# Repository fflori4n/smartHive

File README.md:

# smartHive
smart Hive sistem - ESP32 GSM base, that collects data from multiple atmell based field sensors and sends it via mqtt

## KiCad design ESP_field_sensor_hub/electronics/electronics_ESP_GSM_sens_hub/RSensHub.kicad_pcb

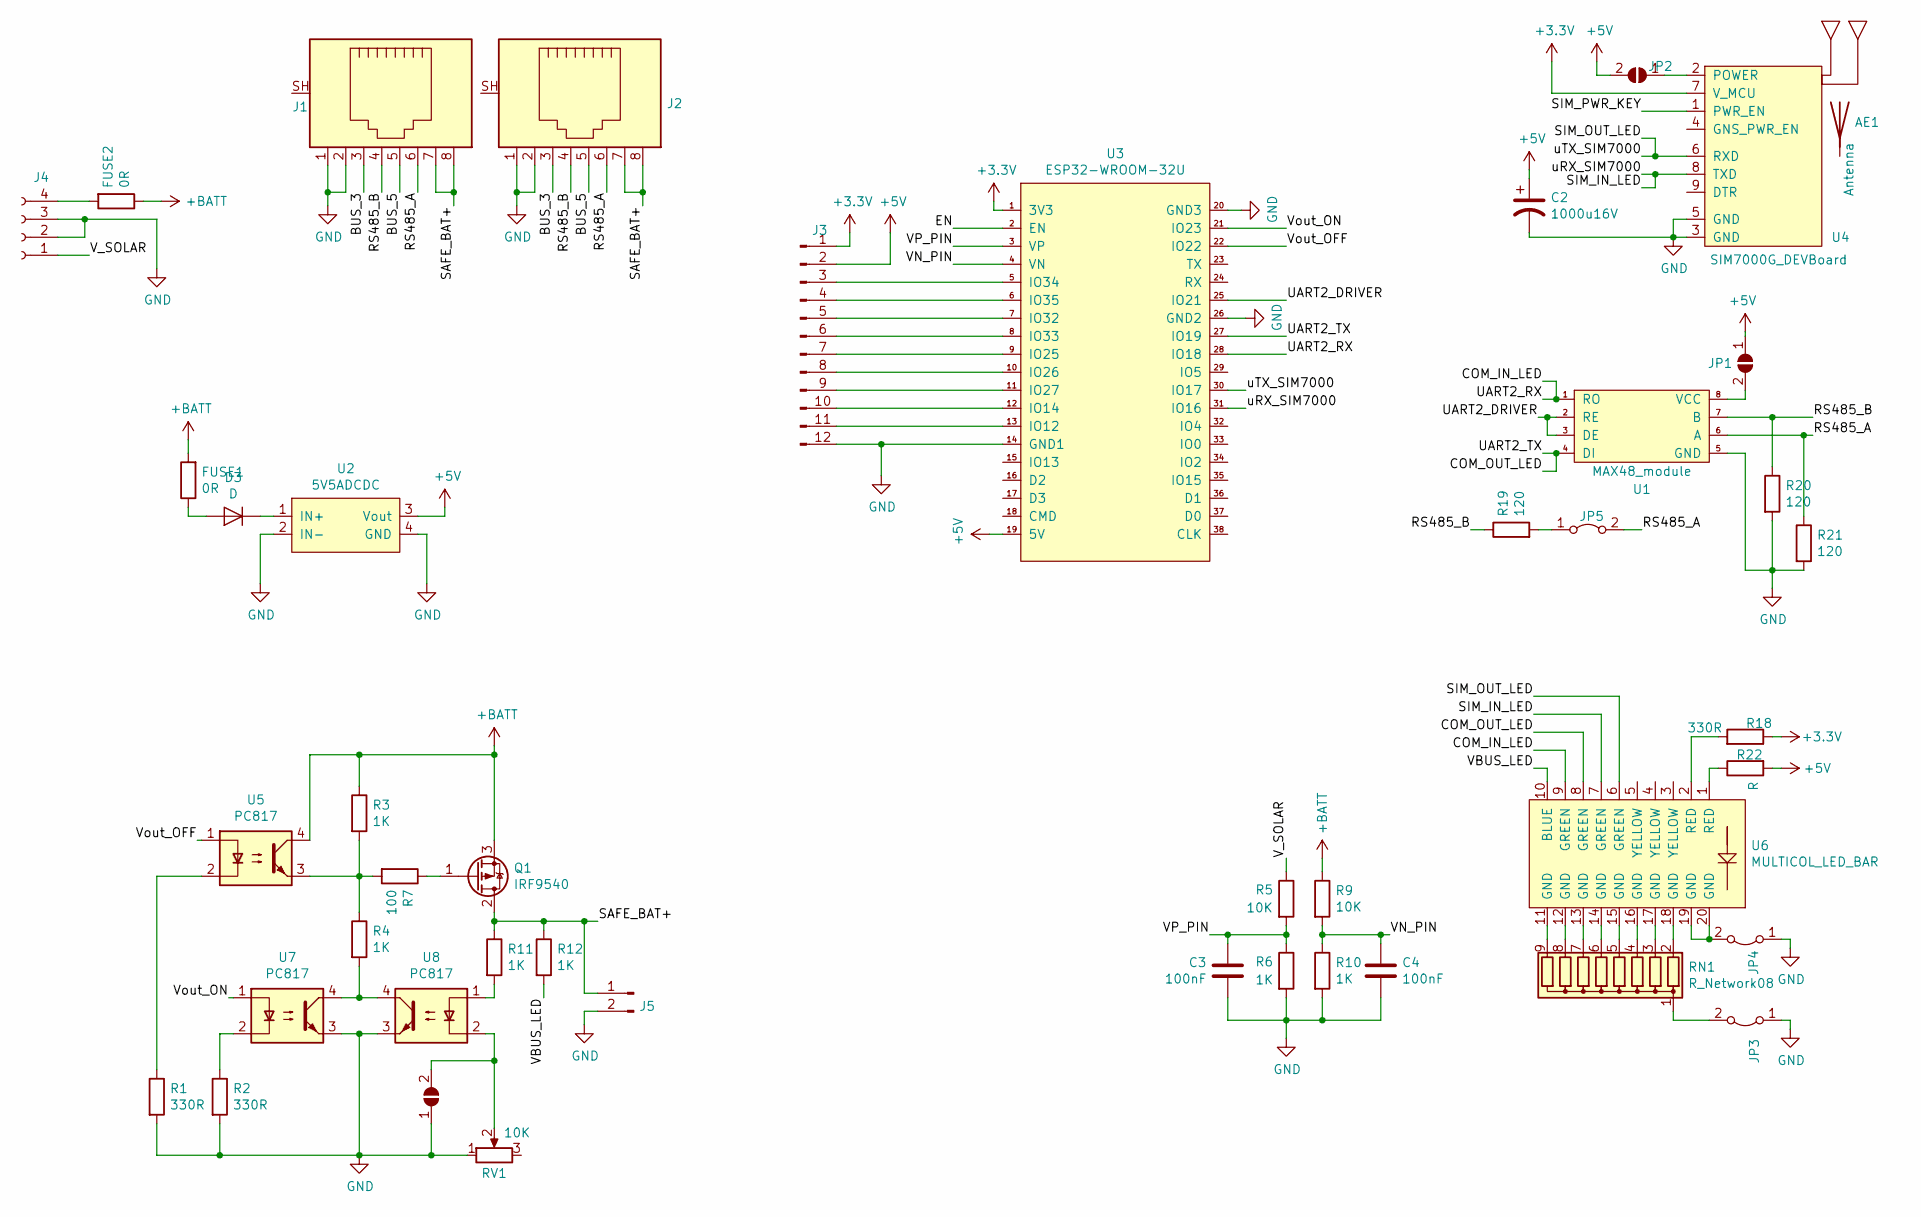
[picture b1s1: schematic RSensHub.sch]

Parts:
AE1: Antenna; GNSSantennaVertical
C2: 1000u16V; CAP_Radial_D10.0mm_P5.00mm
C3, C4: 100nF; Capker_L4.6mm_W2.0mm_P2.50mm
D3: D; 1N41_Diode
FUSE1, FUSE2: 0R; resistor0.25,9mm
J1, J2: RJ45_Shielded; RJ45
J3: Conn_01x12_Male; PinHeader_1x12_P2.54mm_widePads
J4: Conn_01x04_Female; TerminalBlockRemovablex4
J5: Conn_01x02_Male; TerminalBlockRemovablex2
JP1, JP2, JP6: SolderJumper_2_Open; SolderJumper-2_P1.3mm_Open_RoundedPad1.0x1.5mm
JP3, JP4: Jumper_2_Bridged; jumperx2_P2.54mm_widePads
JP5: RS485 terminator; jumperx2_P2.54mm_widePads
Q1: IRF9540; TO-220-3_Horizontal_TabDown_bothSides
R1, R2, R18: 330R; resistor0.25,9mm
R3, R4, R6, R10, R11, R12: 1K; resistor0.25,9mm
R5, R9: 10K; resistor0.25,9mm
R7: 100; resistor0.25,9mm
R19, R20, R21: 120; resistor0.25,9mm
R22: R; resistor0.25,9mm
RN1: R_Network08; PinHeader_1x9_P2.54mm_widePads
RV1: 10K; Potentiometer_ACP_CA9-V10_Vertical_Hole
U1: MAX48_module; MAX485_module
U2: 5V5ADCDC; DCDC_HCW_P715
U3: ESP32-WROOM-32U
U4: SIM7000G_DEVBoard; sim7000G_dev_board
U5, U7, U8: PC817; optoCouplerDIP4
U6: MULTICOL_LED_BAR; DIP-20_LED_BAR_DISP

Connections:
+3V3: J3.1, R18.1, U3.1 (3V3), U4.7 (V_MCU)
+5V: C2.1, J3.2, JP1.1 (A), JP2.2 (B), R22.2, U2.3 (Vout), U3.19 (5V)
+BATT: FUSE1.2, FUSE2.1, Q1.3 (S), R3.1, R9.1, U5.4; also elsewhere on the board
/BUS_3: J1.3, J2.3
/BUS_5: J1.5, J2.5
/COM_IN_LED: U1.1 (RO), U3.28 (IO18), U6.9 (GREEN)
/COM_OUT_LED: U1.4 (DI), U3.27 (IO19), U6.8 (GREEN)
/EN: U3.2 (EN)
/RS485_A: J1.6, J2.6, JP5.2 (B), R21.1, U1.6 (A)
/RS485_B: J1.4, J2.4, R19.1, R20.1, U1.7 (B)
/SAFE_BAT+: J1.7, J1.8, J2.7, J2.8, J5.1, Q1.2 (D), R11.1, R12.1
/SIM_IN_LED: U3.31 (IO16), U4.8 (TXD), U6.7 (GREEN)
/SIM_OUT_LED: U3.30 (IO17), U4.6 (RXD), U6.6 (GREEN)
/SIM_PWR_KEY: U4.1 (PWR_EN)
/UART2_DRIVER: U1.2 (RE), U1.3 (DE), U3.25 (IO21)
/VBUS_LED: R12.2, U6.10 (BLUE)
/VN_PIN: C4.1, R9.2, R10.1, U3.4 (VN)
/VP_PIN: C3.1, R5.2, R6.1, U3.3 (VP)
/V_SOLAR: J4.1, R5.1
/Vout_OFF: U3.22 (IO22), U5.1
/Vout_ON: U3.21 (IO23), U7.1
GND: C2.2, C3.2, C4.2, J1.1, J1.2, J2.1, J2.2, J3.12, J4.2, J4.3, J5.2, JP3.1 (A), JP4.1 (A), JP6.1 (A), R1.2, R2.2, R6.2, R10.2, R20.2, R21.2, RV1.1, U1.5 (GND), U2.2 (IN-), U2.4 (GND), U3.14 (GND1), U3.20 (GND3), U3.26 (GND2), U4.3 (GND), U4.5 (GND), U7.3, U8.3
unnamed: D3.1 (K), U2.1 (IN+)
unnamed 24: D3.2 (A), FUSE1.1; also elsewhere on the board
unnamed 25: FUSE2.2, J4.4; also elsewhere on the board
unnamed: J3.3, U3.5 (IO34)
unnamed: J3.4, U3.6 (IO35)
unnamed: J3.5, U3.7 (IO32)
unnamed: J3.6, U3.8 (IO33)
unnamed: J3.7, U3.9 (IO25)
unnamed: J3.8, U3.10 (IO26)
unnamed: J3.9, U3.11 (IO27)
unnamed: J3.10, U3.12 (IO14)
unnamed: J3.11, U3.13 (IO12)
unnamed: JP1.2 (B), U1.8 (VCC)
unnamed: JP2.1 (A), U4.2 (POWER)
unnamed: JP3.2 (B), RN1.1 (common)
unnamed: JP4.2 (B), U6.19 (GND), U6.20 (GND)
unnamed: JP5.1 (A), R19.2
unnamed: JP6.2 (B), RV1.2, U8.2
unnamed: Q1.1 (G), R7.1
unnamed: R1.1, U5.2
unnamed: R2.1, U7.2
unnamed: R3.2, R4.1, R7.2, U5.3
unnamed: R4.2, U7.4, U8.4
unnamed: R11.2, U8.1
unnamed: R18.2, U6.2 (RED)
unnamed: R22.1, U6.1 (RED)
unnamed: RN1.2 (R1), U6.18 (GND)
unnamed: RN1.3 (R2), U6.17 (GND)
unnamed: RN1.4 (R3), U6.16 (GND)
unnamed: RN1.5 (R4), U6.15 (GND)
unnamed: RN1.6 (R5), U6.14 (GND)
unnamed: RN1.7 (R6), U6.13 (GND)
unnamed: RN1.8 (R7), U6.12 (GND)
unnamed: RN1.9 (R8), U6.11 (GND)

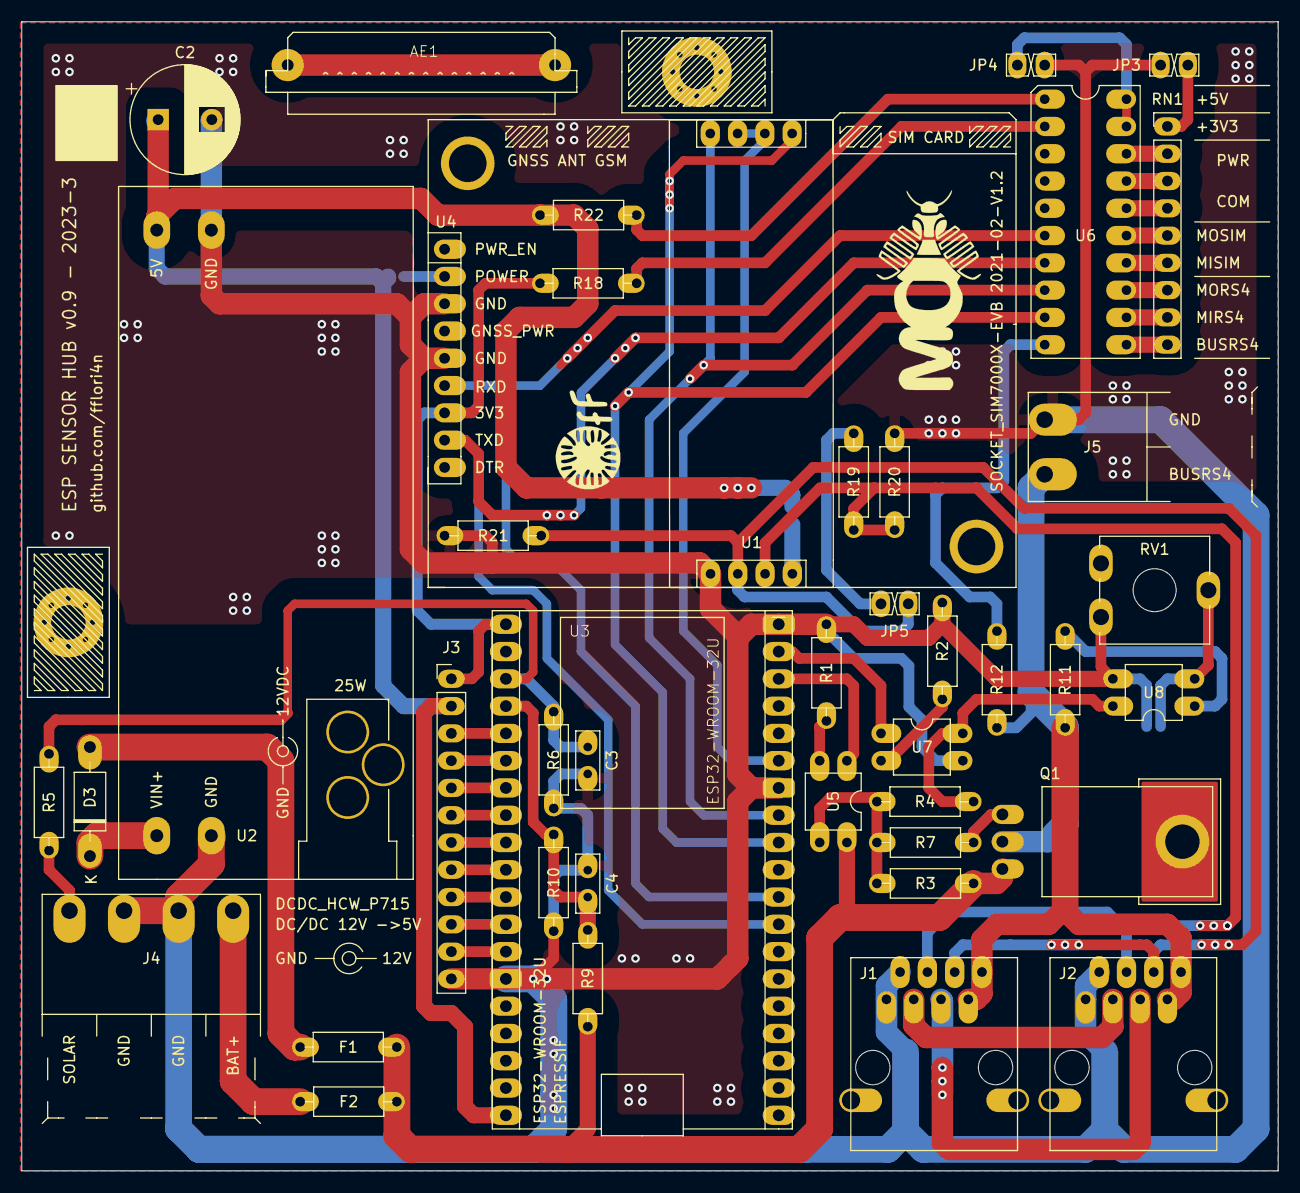
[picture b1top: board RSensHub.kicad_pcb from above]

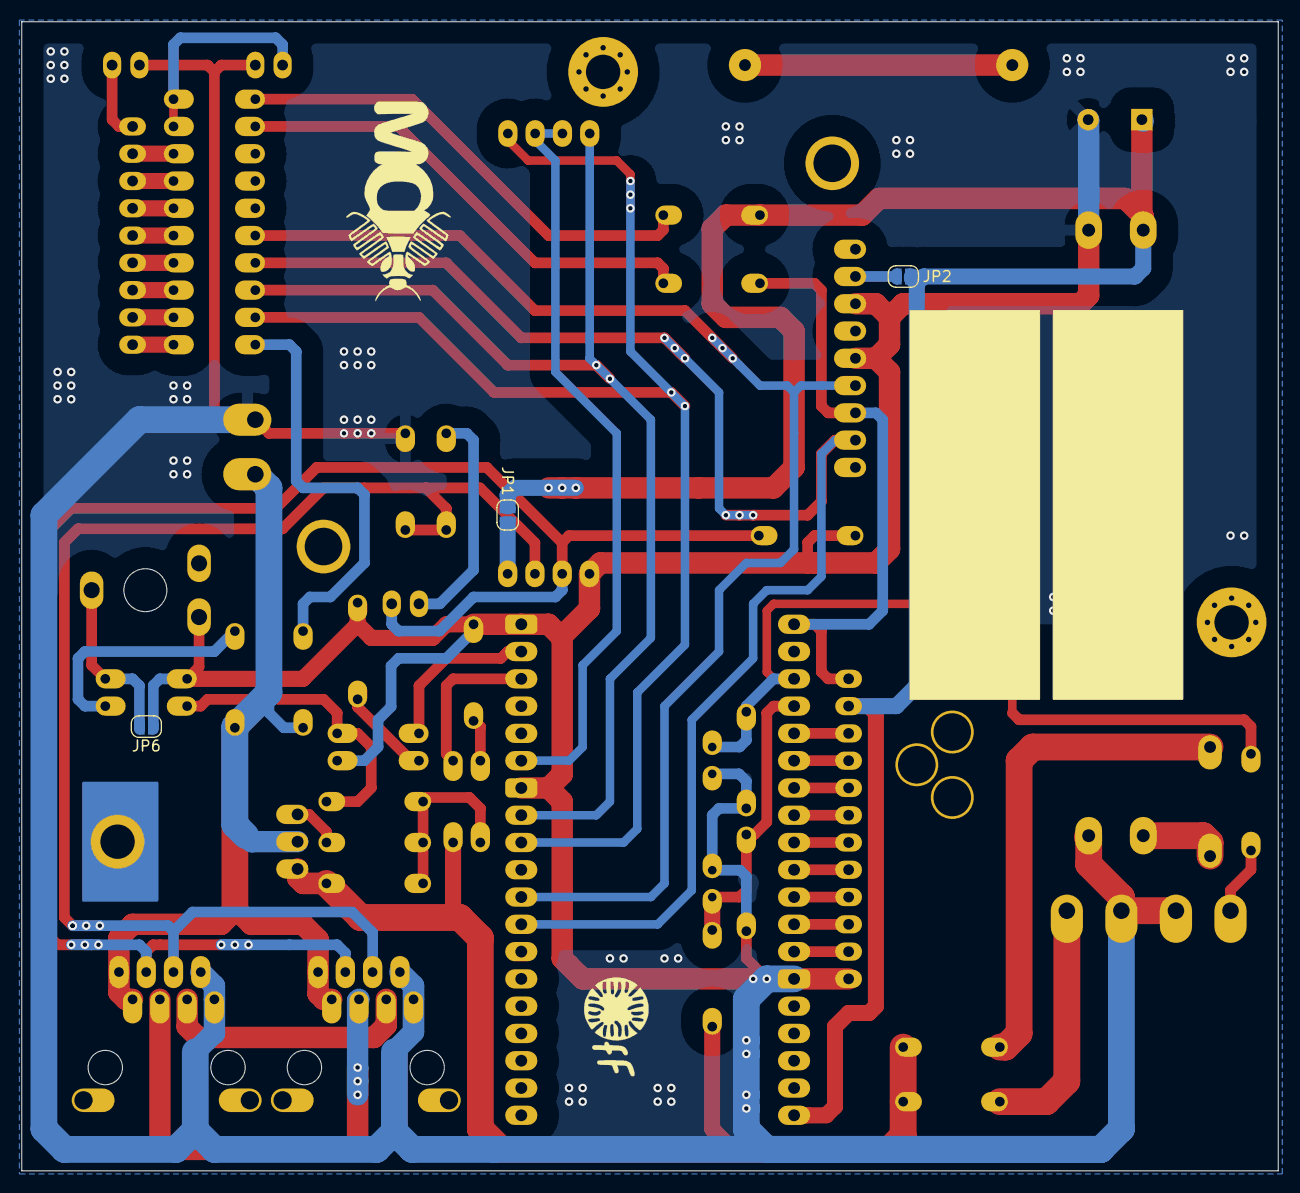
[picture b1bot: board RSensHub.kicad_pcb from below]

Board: 2 copper layers, 117.0 x 107.0 mm, 45 parts (3 on the bottom side), 54 nets.

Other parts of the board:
F1, F2: 0R; resistor0.25,9mm

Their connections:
+BATT: F1.2, F2.1; also elsewhere on the board
unnamed 24: F1.1; also elsewhere on the board
unnamed 25: F2.2; also elsewhere on the board

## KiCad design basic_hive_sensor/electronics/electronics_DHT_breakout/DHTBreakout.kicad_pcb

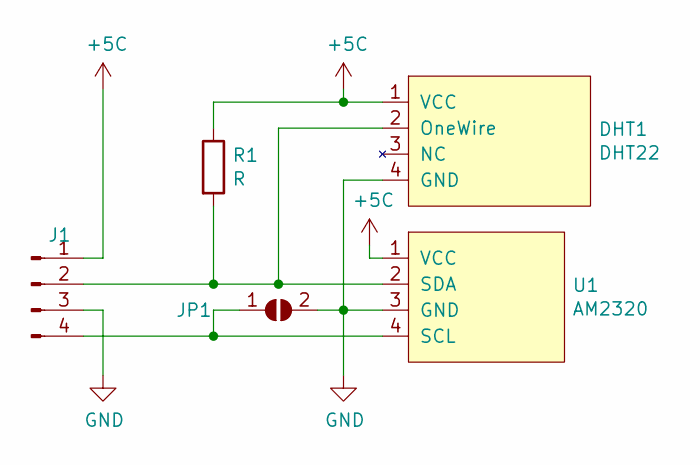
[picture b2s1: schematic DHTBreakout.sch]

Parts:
DHT1: DHT22; DHT_Horiz
J1: Conn_01x04_Male; DHT_4wireCable4mm
JP1: SolderJumper_2_Open; SolderJumper-2_P1.3mm_Open_Pad1.0x1.5mm
R1: R; resistor0.25,9mm
U1: AM2320; AM2320_Horiz

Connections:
+5C: DHT1.1 (VCC), J1.1, R1.1, U1.1 (VCC)
GND: DHT1.4 (GND), J1.3, JP1.2 (B), U1.3 (GND)
unnamed: DHT1.2 (OneWire), J1.2, R1.2, U1.2 (SDA)
unnamed: J1.4, JP1.1 (A), U1.4 (SCL)

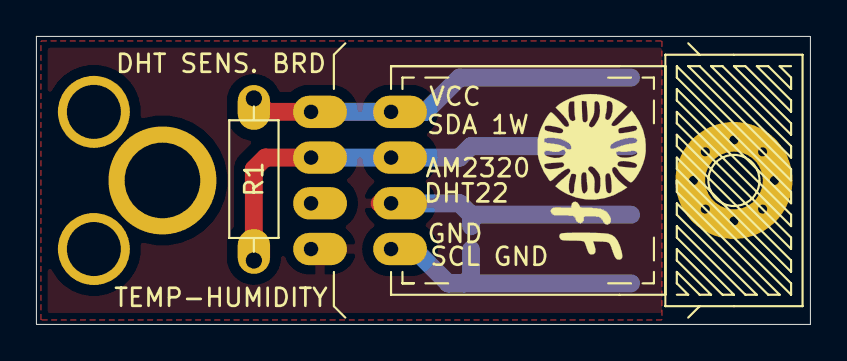
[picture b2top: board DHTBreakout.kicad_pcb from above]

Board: 2 copper layers, 43.0 x 16.0 mm, 5 parts (1 on the bottom side), 4 nets.

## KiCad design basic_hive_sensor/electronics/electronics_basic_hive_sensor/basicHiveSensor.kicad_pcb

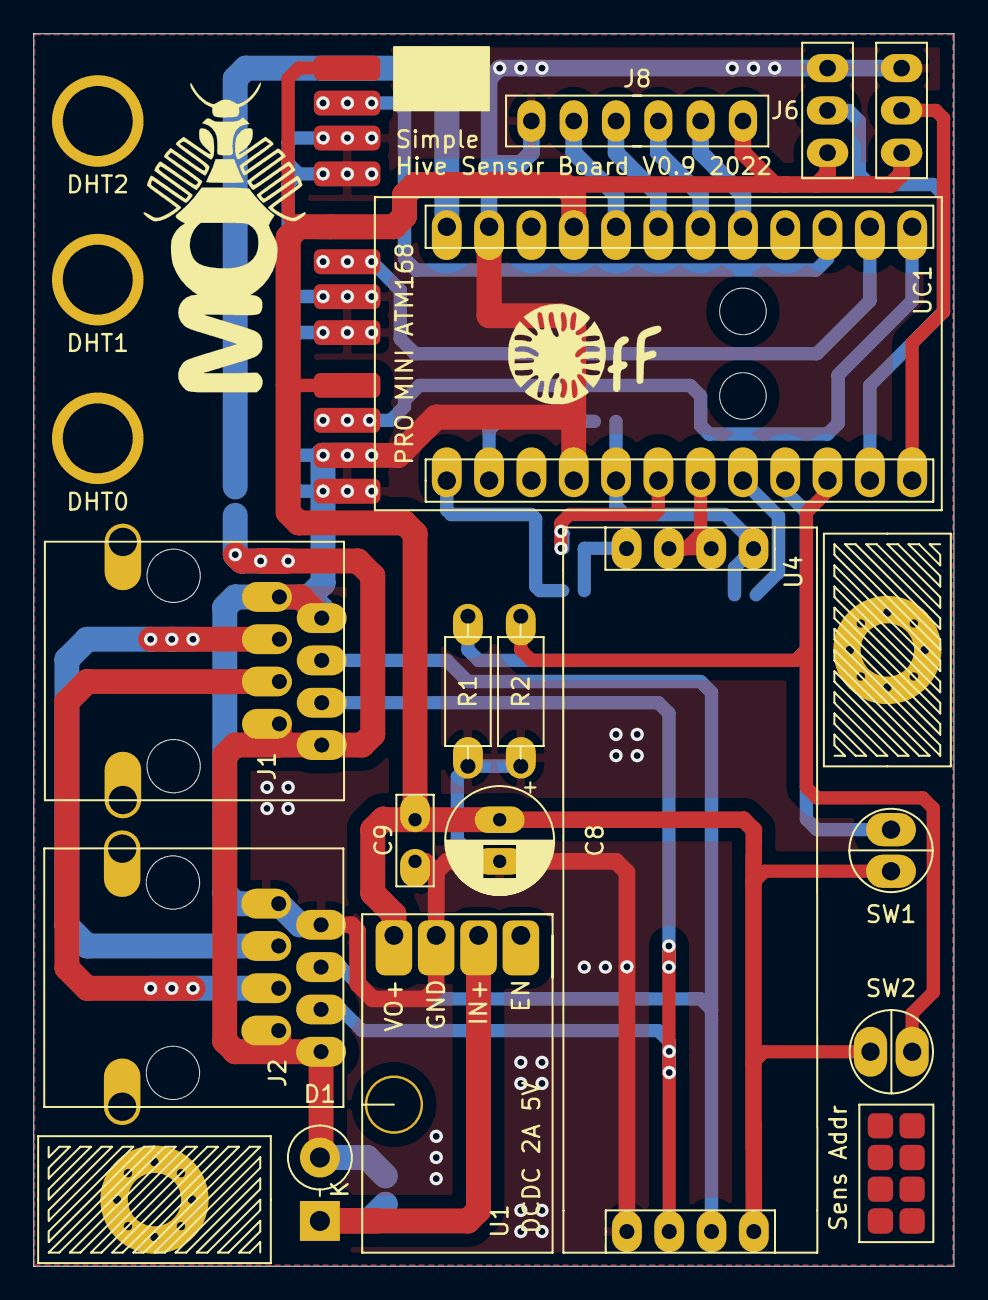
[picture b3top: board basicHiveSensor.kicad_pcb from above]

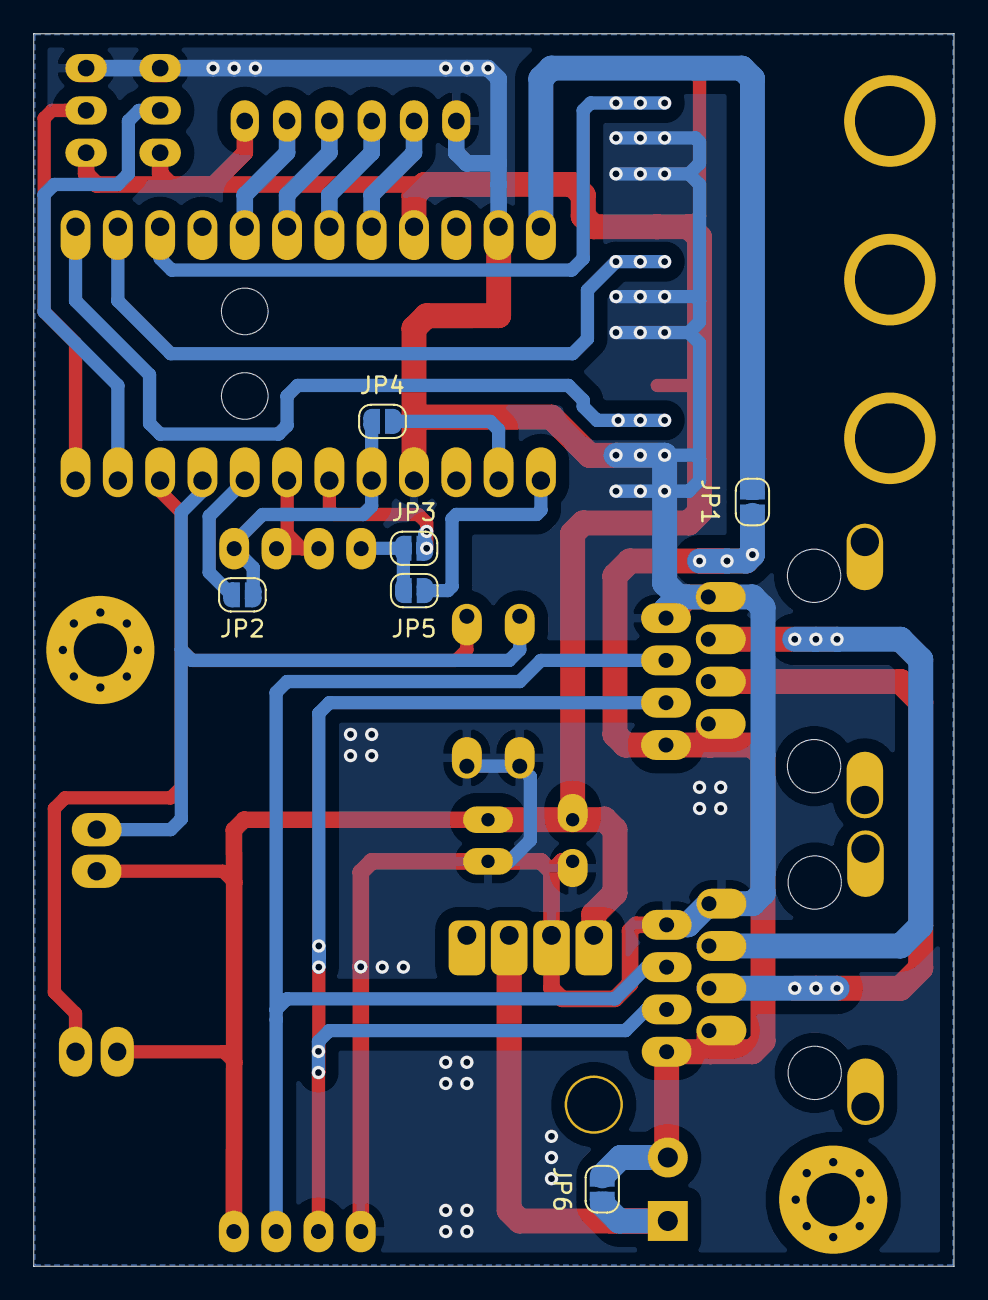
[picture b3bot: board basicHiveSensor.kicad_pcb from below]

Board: 2 copper layers, 55.2 x 74.0 mm, 24 parts (6 on the bottom side), 27 nets.

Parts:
C8: CP1; CAP_Radial_D6.3mm_P2.50mm100uF16V
C9: C; Capker_L4.6mm_W2.0mm_P2.50mm
D1: D_ALT; D_DO-15_P3.81mm_Vertical_KathodeUp
J1, J2: RJ45_Shielded; RJ45
J3, J4, J5: Conn_01x04_Male; Con_CopperPad1.5mmx4x4_withHole
J6, J7: Conn_01x03_Male; PinHeader_1x3_P2.54mm_widePads
J8: Conn_01x06_Male; PinHeader_1x6_P2.54mm_widePads
JP1, JP2, JP3, JP4, JP5, JP6: Sold; SolderJumper-2_P1.3mm_Open_RoundedPad1.0x1.5mm
R1, R2: R; resistor0.25,9mm
SW1, SW2: SW_Push_45deg; SW520-D5.2P2.5
U1: QSKJ_DCDC_1.8,2.5,3.3,5,9,12; Step Down 1.8V 2.5V 3.3V 5V 9V 12V (08-17V) 3A
U4: MAX48_module; MAX485_module
UC1: ProMiniClone; ProMiniCloneSocket_noAnalogPins

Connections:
+5V: C8.1, C9.1, J3.1, J4.1, J5.1, J6.1, J7.1, J8.1, SW1.2, SW2.2, U1.1, U4.8, UC1.9
+BATT: D1.2, J1.7, J1.8, J2.7, J2.8, JP1.1, JP6.2
/DHT0_DATA: J3.2, UC1.1
/DHT1_DATA: J4.2, UC1.2
/DHT2_DATA: J5.2, UC1.3
/GPIO0: R2.2, SW2.1, UC1.22
/GPIO1: R1.2, SW1.1, UC1.21
/GPIO2: J6.2, UC1.23
/GPIO3: J7.2, UC1.24
/GPIO4: J8.2, UC1.5
/GPIO5: J8.3, UC1.6
/GPIO6: J8.4, UC1.7
/GPIO7: J8.5, UC1.8
/MAX485_DE: U4.2, U4.3, UC1.19
/MAX485_DI: JP3.2, JP5.1, U4.4
/MAX485_RO: JP2.2, JP4.1, U4.1, UC1.17
/RS485_A: J1.6, J2.6, U4.6
/RS485_B: J1.4, J2.4, U4.7
/uRXD: JP4.2, UC1.14
/uTXD: JP5.2, UC1.13
GND: C8.2, C9.2, J1.1, J1.2, J2.1, J2.2, J3.3, J3.4, J4.3, J4.4, J5.3, J5.4, J6.3, J7.3, J8.6, R1.1, R2.1, U1.2, U4.5, UC1.11, UC1.16
unnamed: D1.1, JP6.1, U1.3
unnamed: J1.3, J2.3
unnamed: J1.5, J2.5
unnamed: JP1.2, UC1.12
unnamed: JP2.1, UC1.20
unnamed: JP3.1, UC1.18

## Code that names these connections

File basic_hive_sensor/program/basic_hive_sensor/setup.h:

#ifndef USING_SETTINGS_H_RS485CONF
#define USING_SETTINGS_H_RS485CONF

/// BASIC PINOUT

/// - RS485 PINS - 
#define RO_PIN 5//10
#define DI_PIN 3//11
#define DE_PIN 4//12

/// - DHT SENSORS -
#define DHT0_PIN 12
#define DHT1_PIN 11
#define DHT2_PIN 10

/// - OTHER PINS -
#define WAKE_PIN 2
#define PIR_PIN 9
#define GPIO0_PIN 6
#define GPIO1_PIN 7
#define GPIO2_PIN 8
//#define GPIO3_PIN 9

/// - TM PERIODS AND MACROS -
#define DHTREAD_PERIOD_SECS 60
#define ER_NOPOLL_SECONDS (60*15) /// 15mins
#define WAITS_ON_POWERON 3 /// wait secs when power is turned on for sensors and other peripheries to power on properly, before reading them.

#define MOTION_ACTIVATE_PROP 0.1 /// if motion is detected for 10% of DHTREAD PERIOD, motion is detected
#define MOTION_TRIGGER_MODE 1 /// 0 - Zero tolerance for motion, use this when sensor is using power saving mode, motion detection could still return false results, 1 - normal mode
#define READGPIO9 (PINB  & B00000010)



/// - DHT SENSOR OBJECTS -
/// DEFINE DHT SENSORS USED, AND CREATE DHT TYPE OBJECT - COMMENT/UNCOMMENT and CHANGE DHT TYPE
//#define DHT0_TYPE DHT11
#define DHT1_TYPE DHT11
#define DHT2_TYPE DHT22


#ifdef DHT1_TYPE
  DHT dht1(DHT1_PIN, DHT1_TYPE);
#endif
#ifdef DHT2_TYPE
  DHT dht2(DHT2_PIN, DHT2_TYPE);
#endif
#ifdef DHT0_TYPE
  DHT dht0(DHT0_PIN, DHT0_TYPE);
#endif

/// - RS485 CONFIG -
/// RS485 com speed. Keep it low, because of software serial
#define BAUD 9600
/// Addr can't be 0 because translates to '\0' and f*cks up all kinds of string functions!!!
#define THIS_DEV_ADDR 65
#define MASTER_DEV_ADDR 70
#define DEV_TYPE_CHAR 'A'
//#define DEV_IS_MASTER   /// compile with as master (base), or compile as slave (sensor)

#endif

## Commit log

2022-12-19 initial commit.
2022-12-20 Mqtt info msg is sent succesfully. But very hacky, needs c-string magic fuckey to work better
2022-12-21 mqtt status report cleaned up. gnss parsing cleaned up.
2022-12-22 wrote formating function to drop trailing zeros and decimals from gnss height string
2022-12-22 reading voltage and adding to mqtt message ( very cursed but works ), voltage measurement is incorrect, TODO: fix it
2022-12-24 Added LUT for rssi sim7000 to dBm conversion Sending mqtt every 10mins for testing
2022-12-30 Crated footprints for GSM board and Antenna and changed up status LEDs
2022-12-30 Previous
2022-12-30 Added debug tool used for testing basic_hive_sensor RS485 communication
2022-12-30 TODO: Found huge bug, needs fixing - if crc bit is '\0' whole cstring system breaks Sender will not send string, reciever will not parse string.
    commented out all sim functionality for now, rework and optimise whole RS485Com.h before doing anything else.
    pins 18,19,21 work OK on the ESP for the RS485 uart, connect them on the schematic
2023-01-03 Added poll sending capability to RS485Com.h
2023-01-03 Did some cleaning up and commenting, master works now, next: slave, copy string into shared buffer, and everyone has to use the same function for CRC, start/ stop and sending
2023-01-03 Fixed '\0' issue probably... but addresess should still be alphanumeric Unified sending and encoding function
2023-01-04 Got two sensors to work, communication and addressing is OK so far. AM2320 is the same sensor as DHT22 so the standard DHT.h library can deal with it fine
2023-01-05 worked on basic hive
    added method for getting DHT sensor data, checking if data is valid and averageing sensor values
    changed - rearanged interrupt and sleep functions
    changed - DHT sensor reading is done triggered by timer interrupt
    added PIR or microwave motion detector support - works with polling, but should really be interrupt. - pinchange interrupt conflicts with software serial - does it worth migrating to new soft serial 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
    added warning light when module did not get poll from master for some time
2023-01-07 Working on ESP sensor class
2023-01-07 wrote BasicHiveSensor.h, can define sensors, can set address timeout for sensors, has functions for polling and parsing sensor data - parsing is not working, gona change the format to be easily parse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
2023-01-07 damn C. had to write parser to convert string to double, still not working for last two tags :(
2023-01-08 fixed CSV parsing with dirty fix, needs more work. Added mqtt string creation to basicHive class - TODO: strlcat instead of strcat everywhere to avoid buff overflow & separate mqtt payload string cre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
2023-01-08 separated out functions to put reformated BHsensor data into mqtt msg payload buff, aswell as data from SIM7000 status, TODO: the two will use the same function for sending mqtt
2023-01-08 mqtt working for both types - Sofware serial does not for some reason work for RS485 and SIM uarts at the same time, using HWserial for sim now. Heavy cleanup needed.
2023-01-09 Basic hive sensor - made the DHT reading more reliable, added internal pullups for data lines. PIR sensor is now polled in ISR, working. added ifdef-s for unused DHT sensors
2023-01-10 worked on sens hub PCB
2023-02-03 short circuit protection - tested on dot board, ESP control pins not connected
2023-02-04 GPIO 22 and 23 set turn the sensor bus power on or off
2023-02-04 worked on sens hub PCB layout, mostly done, needs finishing touches
2023-02-05 routed and copper poutred PCB for ESP sensor hub TODO: labels and PCB logos
2023-03-26 started working on GNSS time and NTP functionality, ESP32 timekeeping works, just need to update it from modem. need to parse the GNSS status for string. Played around with chatGPT, and got a fairly 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
2023-03-27 Refactoring SIM7000, writing function for not spaghetti parsing of GNSS CSV string @TODO: not finished
2023-03-30 CGINF CSV parser working, time update working, update every X mins working
2023-04-02 Added sensor response tracking to detect is sensor is offline, added multiple poll request sending when sensor does not respond. Fixed voltage double to mqtt string conversion bug. @TODO: JSON parsin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
2023-04-05 added timed sensor reading and mqtt sending, mqtt msg should arrive every 5 minutes at 0 or 5 min mark.
2023-04-29 trying to fix, wrong value read when power is interrupted, optimised code, com is now priority, sensor will wait a few seconds before reading sensors when power is turned on. Moved all config macros 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
2023-04-30 bugfix of temp/humidity errors( hopefully ), 2 secs should pass between dht sensor polls, DHT library has inbuilt waiting period, and if read.temperature() and read.humidity() are called one after th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
2023-05-06 added second mode of internet connectivity, modem can now use both Wi-Fi using PubSubClient library, and GSM, one is primary, other is backup device. Replaced 10K pull-up resistors with 4K7 on one wi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
2023-07-23 deployed from solar panel in the yard.
2023-08-05 made prototype MCU for logging solar charge current, voltage and bat temp, connected it to Gateway using bitbanged UART, but only one direction, added mqtt tags
2023-08-13 better filtration for solar logger values, and some mqtt msg changes
2023-08-19 removed solar logger and integrated sensors into main rtu, removed current sensor because it's measurements were erratic, probably max current rating is too low for this application, and sensor got f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
2023-11-25 added watchdog timer and sending reboot reason and memory debug info to server, sim7000 firmware can sometimes freeze and need a power cycle to come online - mayor headace but mostly does not happen,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
2023-12-09 fixed negative temp bug, added periodic reset of SIM7000 and PSM power saving mode
2023-12-26 added external power cutoff for low battery, corrected error handling of SIM AT commands, todo: still more work to be done here.
2024-06-15 SIM class rework to clean up and add functions for common actions, and fixed parsing of responses since I'm a professional now and had to make it less shit
2024-07-02 fixed annoying software serial incompatibility, now using 3 Hardware UARTs on ESP and SW on ATM168
